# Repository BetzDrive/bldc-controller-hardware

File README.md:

# Betz Drive - A BLDC Controller

This board is designed for low-speed, high torque motor applications that require
highly precise positional and torque commands.

## Features

 * Chainable Initialization. Input/output connectors and 'disco-bus' pins provide
 dynamic initialization, allowing for easy replacement of any board (no hard coded ids).
 
 * High Precision Current Readings
 
 * 12-bit Precision Positional Readings [AS5047U-HTSM](https://ams.com/documents/20143/36005/AS5047U_DS000637_1-00.pdf)
 
 * Thermal Sensitivity
 
 * Optional 20-pin header with 9 GPIO pins, I2C, 3.3V rail, and ground for add-on functionality!
 
## Renderings

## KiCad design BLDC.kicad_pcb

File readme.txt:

File names:
bldc-controller-B.Cu.gbr: Bottom copper
bldc-controller-B.Mask.gbr: Bottom soldermask
bldc-controller-B.Paste.gbr: Bottom paste stencil
bldc-controller-B.SilkS.gbr: Bottom silkscreen
bldc-controller-F.Cu.gbr: Top copper
bldc-controller-F.Mask.gbr: Top soldermask
bldc-controller-F.Paste.gbr: Top paste stencil
bldc-controller-F.SilkS.gbr: Top silkscreen
bldc-controller-In1.Cu.gbr: Inner layer adjacent to top
bldc-controller-In2.Cu.gbr: Inner layer adjacent to bottom
bldc-controller.drl: Drill file

Notes:
EDA software: KiCad
Overall board dimensions: 60 mm x 60 mm (2.36 x 2.36 in)
The two narrow (13 x 0.5 mm) "pads" on the bottom layer are part of a net tie and should be covered by soldermask.

Contact information:
<EMAIL ADDRESS>
<PHONE NUMBER>

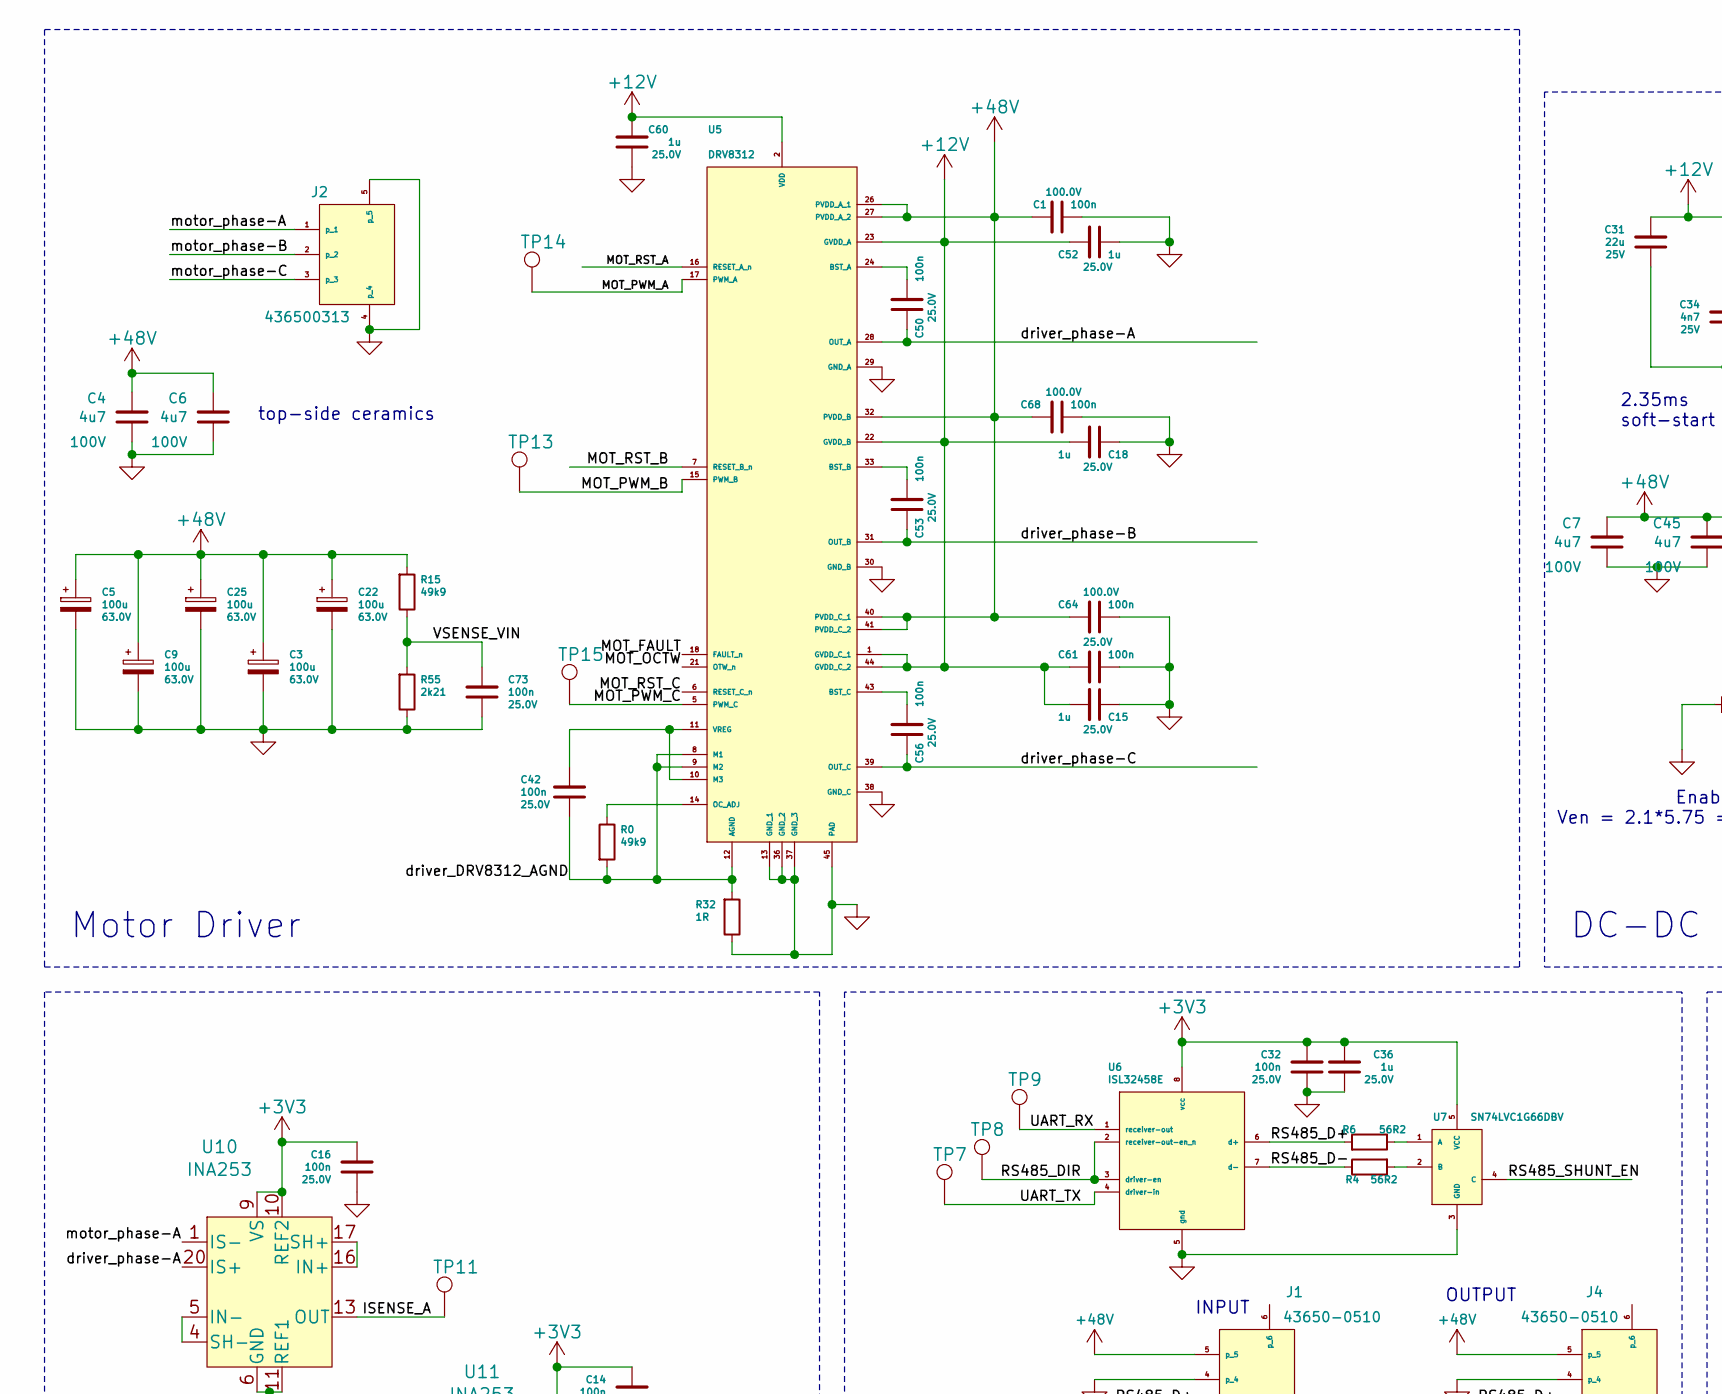
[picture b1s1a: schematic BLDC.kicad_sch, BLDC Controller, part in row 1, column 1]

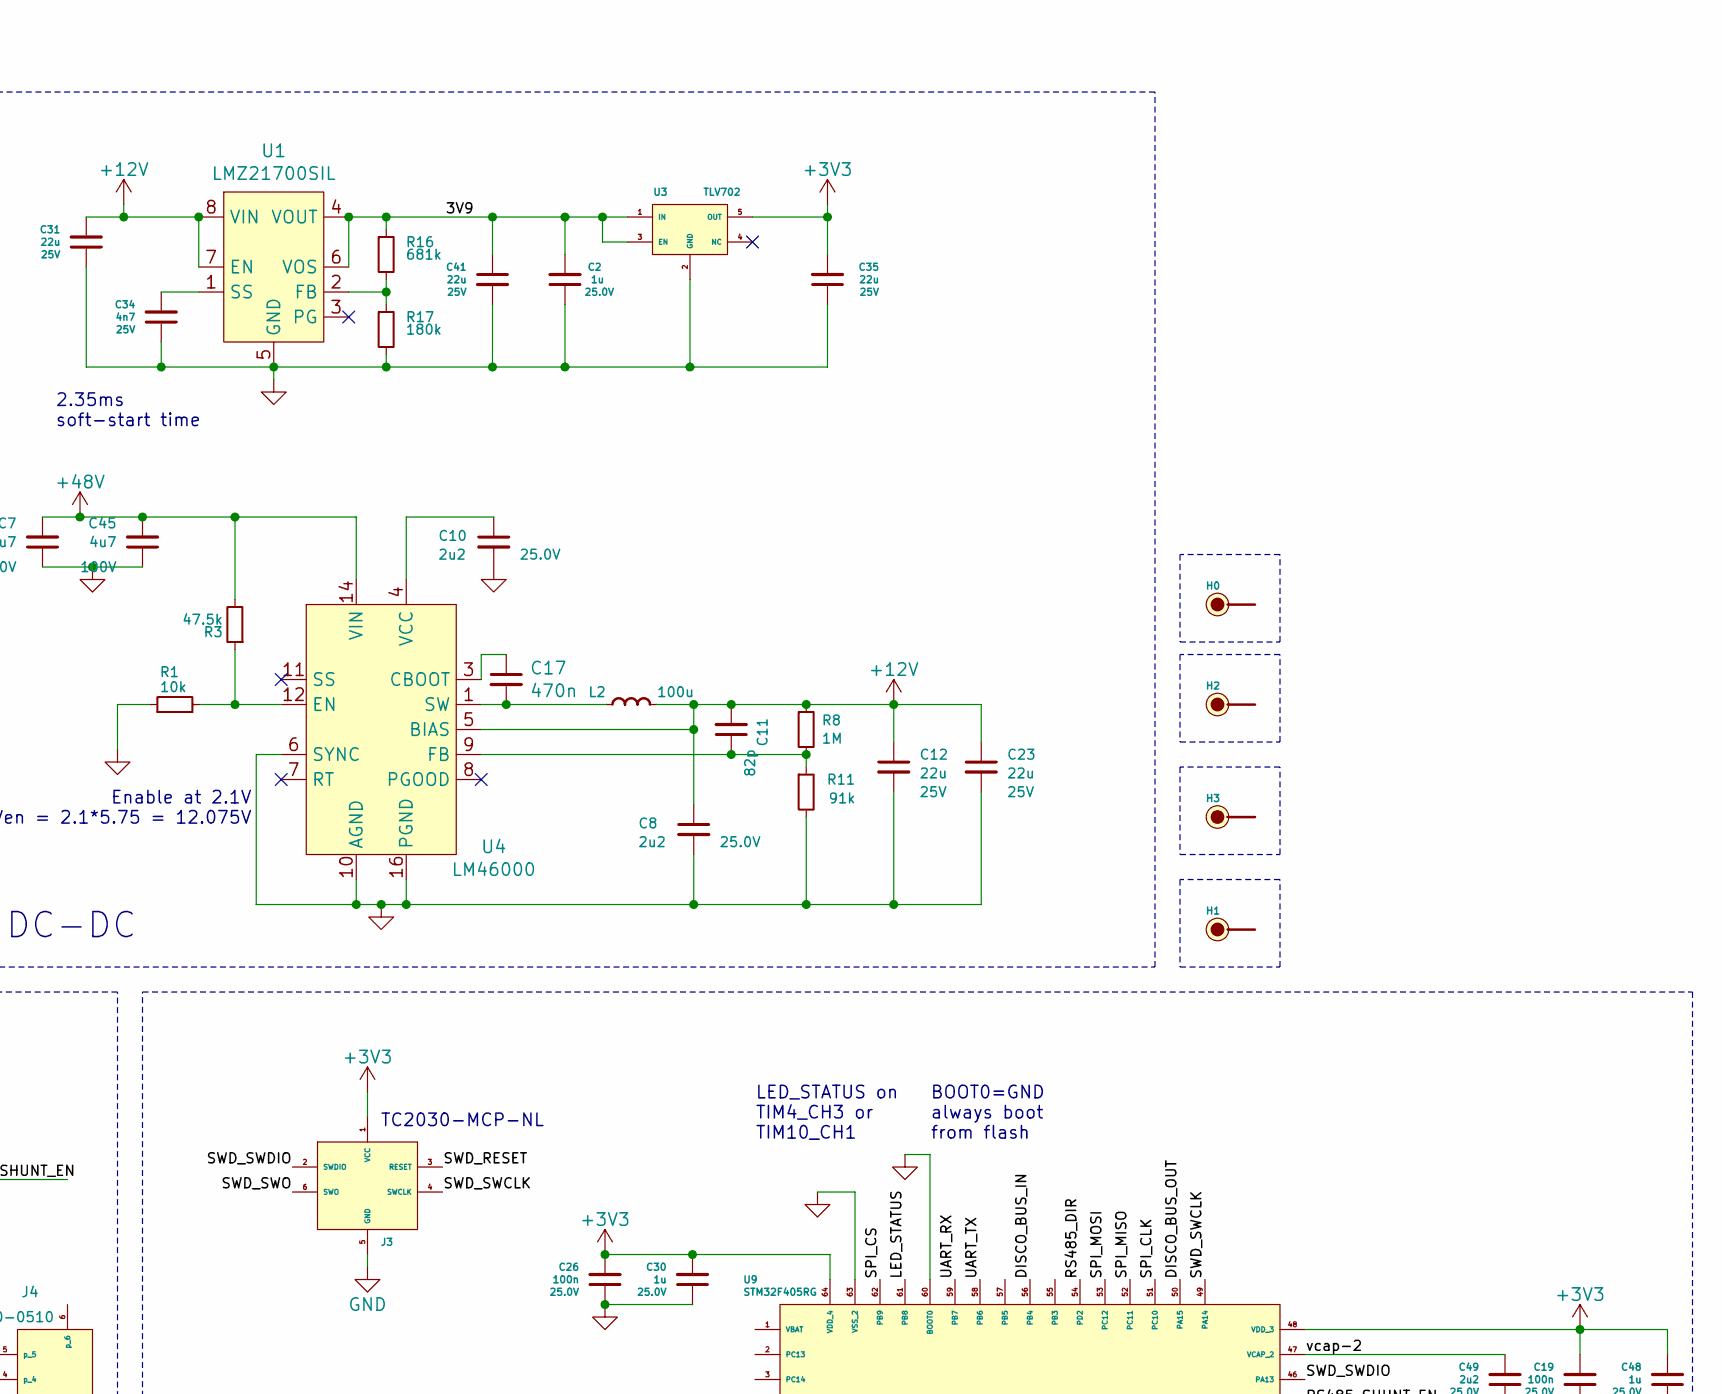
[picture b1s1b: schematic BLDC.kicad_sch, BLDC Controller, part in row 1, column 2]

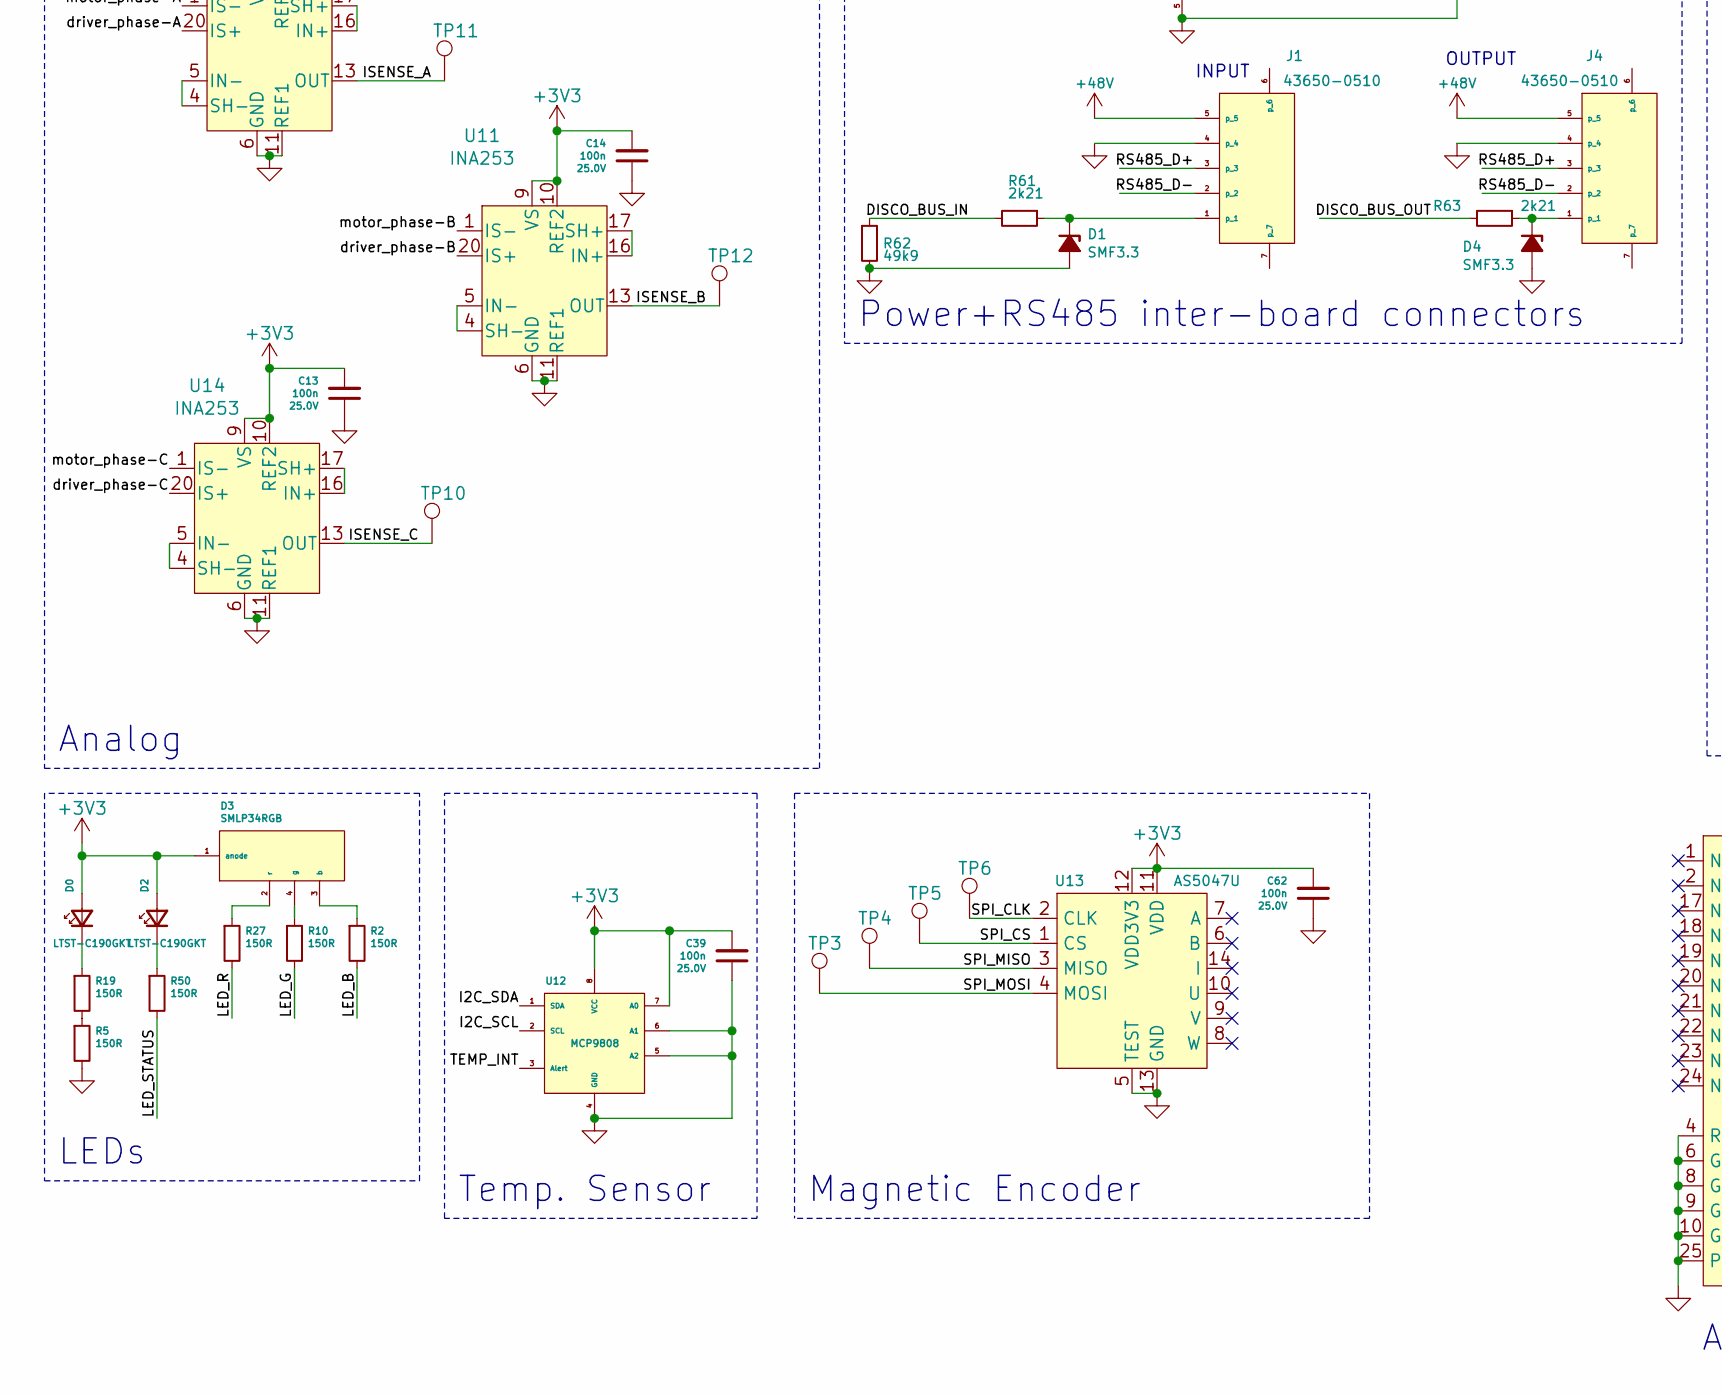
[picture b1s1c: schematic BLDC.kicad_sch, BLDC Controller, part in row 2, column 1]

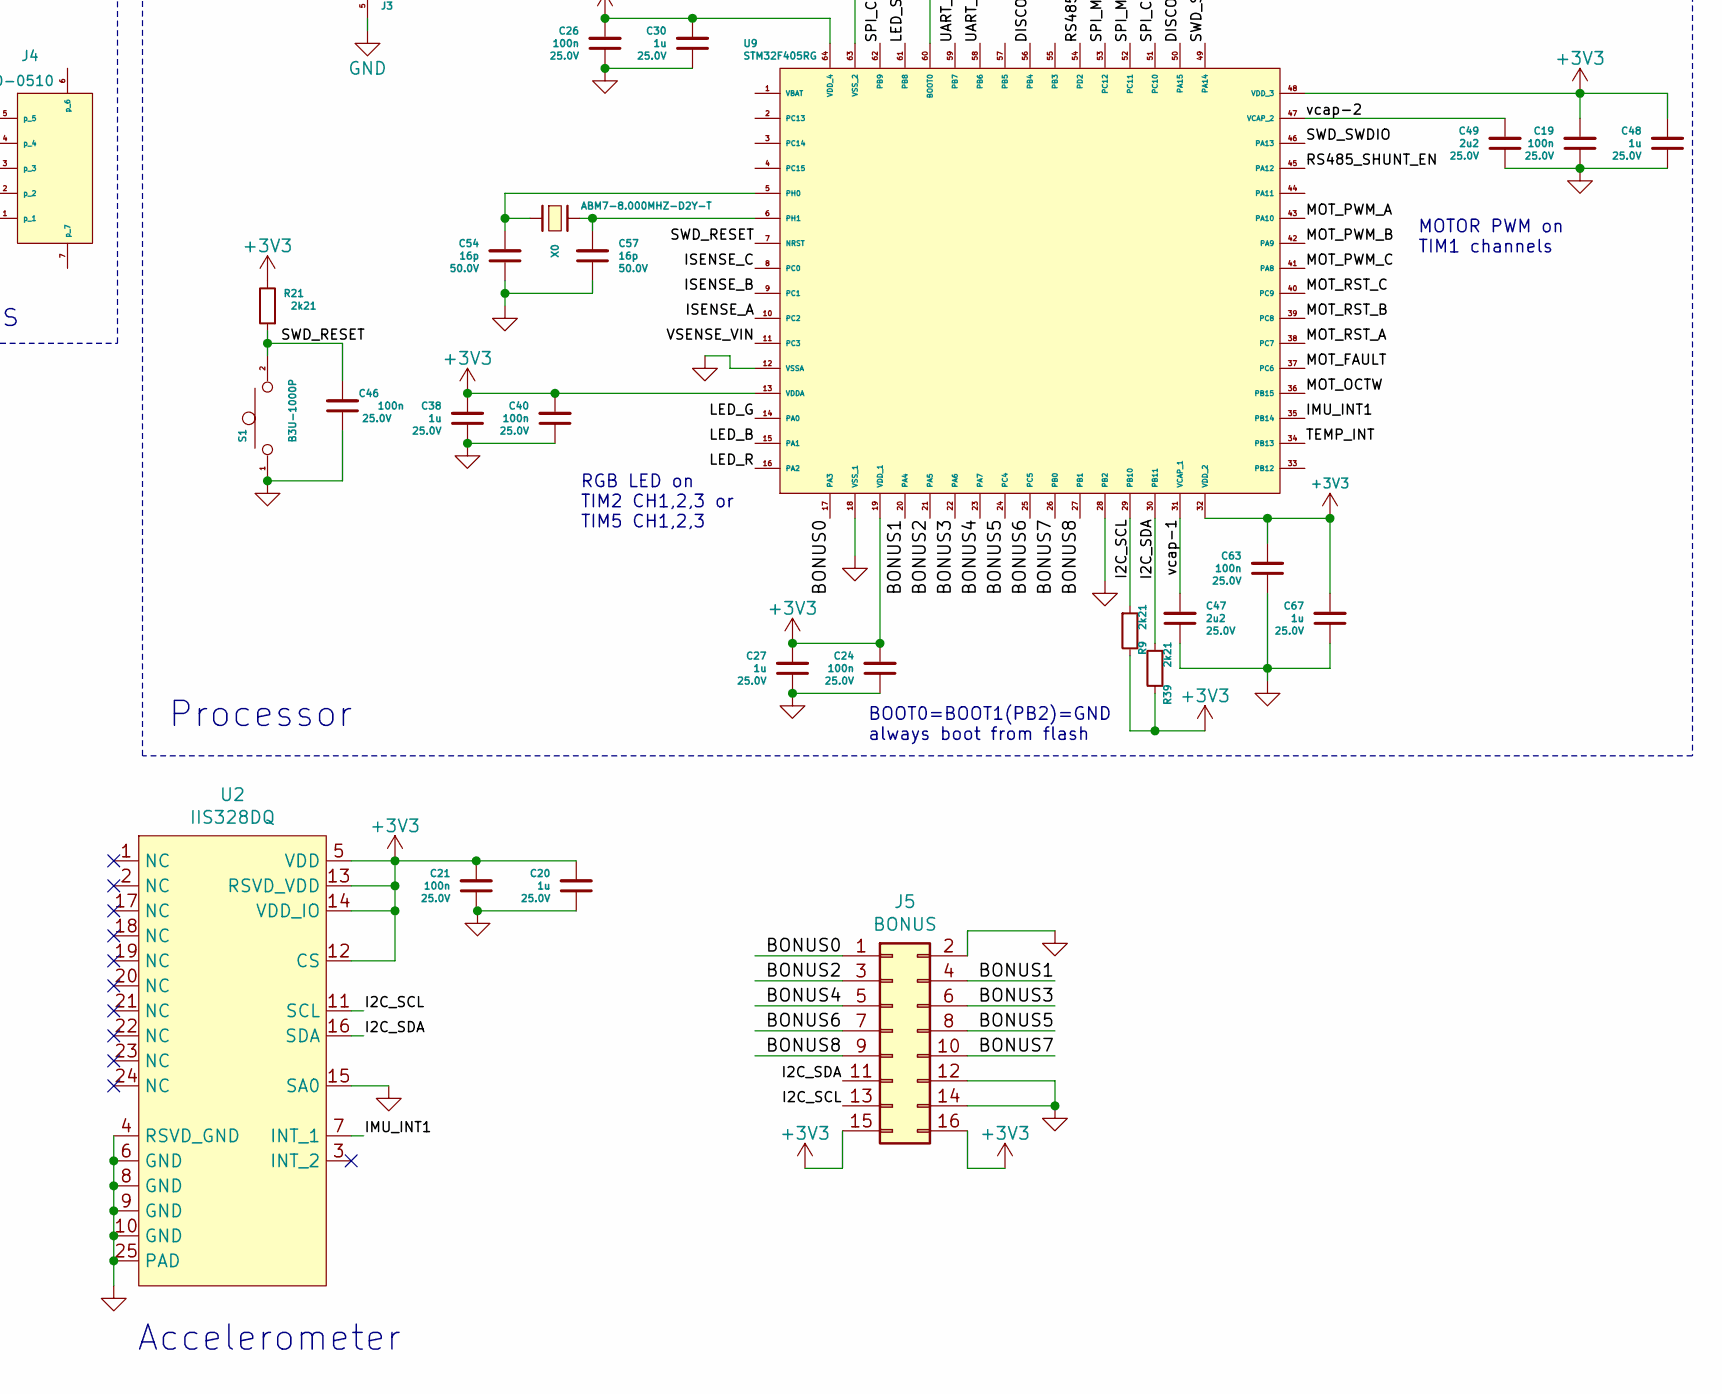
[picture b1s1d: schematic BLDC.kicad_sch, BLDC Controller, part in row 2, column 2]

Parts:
C1, C64, C68: 100n; C_0603_1608Metric; Maximum Voltage 100.0V; Tolerance 10%; MPN CL10B104KC8NNNC
C2, C15, C18, C20, C27, C30, C36, C38, C48, C52, C60, C67: 1u; C_0402_1005Metric; Maximum Voltage 25.0V; Tolerance 10%; MPN GRM155R61E105KA12D
C3, C5, C9, C22, C25: 100u; CP_Elec_10x10; Maximum Voltage 63.0V; Tolerance 20%; MPN EEE-1JA101P
C4, C6, C7, C45: 4u7; C_1210_3225Metric; Maximum Voltage 100V; Tolerance 10%; MPN C3225X7S2A475K200AB
C8, C10, C47, C49: 2u2; C_0402_1005Metric; Maximum Voltage 25.0V; Tolerance 10%; MPN GRM155R61E225KE11D
C11: 82p; C_0402_1005Metric; Maximum Voltage 50V; Tolerance 10%; MPN 04025A820FAT2A
C12, C23, C31, C35, C41: 22u; C_1210_3225Metric; Maximum Voltage 25V; Tolerance 10%; MPN CL32A226KAJNNNE
C13, C14, C16, C19, C21, C24, C26, C32, C39, C40, C42, C46, C50, C53, C56, C61, C62, C63, C73: 100n; C_0402_1005Metric; Maximum Voltage 25.0V; Tolerance 10%; MPN CL05A104KA5NNNC
C17: 470n; C_0402_1005Metric; Maximum Voltage 10.0V; Tolerance 10%; MPN CL05A474KP5NNNC
C34: 4n7; C_0402_1005Metric; Maximum Voltage 25V; Tolerance 10%; MPN CC0402KRX7R8BB472
C54, C57: 16p; C_0402_1005Metric; Maximum Voltage 50.0V; Tolerance 5%; MPN GJM1555C1H160GB01D
D0, D2: LTST-C190GKT; D_0603_1608Metric; MPN LTST-C190GKT
D1, D4: SMF3.3; D_SOD-123F; MPN SMF3.3
D3: SMLP34RGB; rhom-SMLP34RGB-fp; MPN SMLP34RGB2W3
H0, H1, H2, H3: NONE; mounting-hole-pkg
J1, J4: 43650-0510; molex-436500511; MPN 436500510
J2: 436500313; molex-microfit-3-pkg; MPN 436500313
J3: DNP; TC2030-MCP-NL-pkg; MPN DNP
J5: BONUS; PinHeader_2x08_P2.54mm_Horizontal; MPN DNP
L2: 100u; L_7.3x7.3_H4.5; Tolerance 20%; MPN 744777920
R0, R15, R62: 49k9; R_0603_1608Metric; Tolerance 1%; MPN ERJ-3EKF4992V
R1: 10k; R_0402_1005Metric; Tolerance 1%; MPN AC0402FR-0710KL
R2, R5, R10, R19, R27, R50: 150R; R_0402_1005Metric; Tolerance 1%; MPN ERJ-2RKF1500X
R3: 47.5k; R_0402_1005Metric; Tolerance 1%; MPN RC0402FR-0747K5L
R4, R6: 56R2; R_0402_1005Metric; Tolerance 1%; MPN RC0402FR-0756R2L
R8: 1M; R_0402_1005Metric; Tolerance 1%; MPN RC0402FR-071ML
R9, R21, R39, R55, R61, R63: 2k21; R_0402_1005Metric; Tolerance 1%; MPN ERJ-2RKF2211X
R11: 91k; R_0402_1005Metric; Tolerance 1%; MPN RC0402FR-0791KL
R16: 681k; R_0402_1005Metric; Tolerance 1%; MPN RC0402FR-07681KL
R17: 180k; R_0402_1005Metric; Tolerance 1%; MPN RC0402FR-07180KL
R32: 1R; R_0805_2012Metric; Tolerance 1%; MPN ERJ-6DQF1R0V
S1: B3U-1000P; SW_B3U-1000P; MPN B3U-1000P
TP3, TP4, TP5, TP6, TP7, TP8, TP9, TP10, TP11, TP12, TP13, TP14, TP15: TestPoint; TestPoint_Pad_D1.0mm
U1: LMZ21700SIL; SIL0008E; MPN LMZ21700SILR
U2: IIS328DQ; QFN-24-1EP_4x4mm_P0.5mm_EP2.6x2.6mm; MPN IIS328DQTR
U3: TLV702; SOT-23-5; MPN TLV70233DBVR
U4: LM46000; PWP0016G; MPN LM46000PWPR
U5: DRV8312; HTSSOP-44; MPN DRV8312DDWR
U6: ISL32458E; SOIC-8_3.9x4.9mm_P1.27mm; MPN ISL32458EIBZ-T7A
U7: SN74LVC1G66DBV; SOT-23-5; MPN SN74LVC1G66DBV
U9: STM32F405RG; LQFP-64_10x10mm_P0.5mm; MPN STM32F405RGT6
U10, U11, U14: INA253; TSSOP-20_4.4x6.5mm_P0.65mm; MPN INA253A2IPW
U12: MCP9808; MSOP-8_3x3mm_P0.65mm; MPN MCP9808T-E/MS
U13: AS5047U; TSSOP-14_4.4x5mm_P0.65mm; MPN AS5047U-HTSM
X0: ABM7-8.000MHZ-D2Y-T; ABM7-8MHZ-D2Y-T-pkg; MPN ABM7-8.000MHZ-D2Y-T

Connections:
+3V3: C13.2, C14.2, C16.2, C19.2, C20.2, C21.2, C24.2, C26.2, C27.2, C30.2, C32.2, C35.2, C36.2, C38.2, C39.2, C40.2, C48.2, C62.2, C63.2, C67.2, D0.2 (A), D2.2 (A), D3.1 (anode), J3.1 (VCC), J5.15, J5.16, R9.2, R21.2, R39.2, U2.5 (VDD), U2.12 (CS), U2.13 (RSVD_VDD), U2.14 (VDD_IO), U3.5 (OUT), U6.8 (vcc), U7.5 (VCC), U9.13 (VDDA), U9.19 (VDD_1), U9.32 (VDD_2), U9.48 (VDD_3), U9.64 (VDD_4), U10.9 (VS), U10.10 (REF2), U11.9 (VS), U11.10 (REF2), U12.7 (A0), U12.8 (VCC), U13.11 (VDD), U13.12 (VDD3V3), U14.9 (VS), U14.10 (REF2)
+12V: C8.1, C11.2, C12.1, C15.2, C18.2, C23.1, C31.2, C52.2, C60.2, C61.2, L2.2 (p), R8.1, U1.7 (EN), U1.8 (VIN), U4.5 (BIAS), U5.1 (GVDD_C_1), U5.2 (VDD), U5.22 (GVDD_B), U5.23 (GVDD_A), U5.44 (GVDD_C_2)
+48V: C1.2, C3.1, C4.2, C5.1, C6.2, C7.2, C9.1, C22.1, C25.1, C45.2, C64.2, C68.2, J1.5 (p), J4.5 (p), R3.2, R15.1, U4.13 (VIN), U4.14 (VIN), U5.26 (PVDD_A_1), U5.27 (PVDD_A_2), U5.32 (PVDD_B), U5.40 (PVDD_C_1), U5.41 (PVDD_C_2)
/3V9: C2.2, C41.1, R16.1, U1.4 (VOUT), U1.6 (VOS), U3.1 (IN), U3.3 (EN)
/BONUS0: J5.1, U9.17 (PA3)
/BONUS1: J5.4, U9.20 (PA4)
/BONUS2: J5.3, U9.21 (PA5)
/BONUS3: J5.6, U9.22 (PA6)
/BONUS4: J5.5, U9.23 (PA7)
/BONUS5: J5.8, U9.24 (PC4)
/BONUS6: J5.7, U9.25 (PC5)
/BONUS7: J5.10, U9.26 (PB0)
/BONUS8: J5.9, U9.27 (PB1)
/DISCO_BUS_IN: R61.2, R62.1, U9.56 (PB4)
/DISCO_BUS_OUT: R63.2, U9.50 (PA15)
/I2C_SCL: J5.13, R9.1, U2.11 (SCL), U9.29 (PB10), U12.2 (SCL)
/I2C_SDA: J5.11, R39.1, U2.16 (SDA), U9.30 (PB11), U12.1 (SDA)
/IMU_INT1: U2.7 (INT_1), U9.35 (PB14)
/ISENSE_A: TP11.1, U9.10 (PC2), U10.13 (OUT)
/ISENSE_B: TP12.1, U9.9 (PC1), U11.13 (OUT)
/ISENSE_C: TP10.1, U9.8 (PC0), U14.13 (OUT)
/LED_B: R2.2, U9.15 (PA1)
/LED_G: R10.2, U9.14 (PA0)
/LED_R: R27.2, U9.16 (PA2)
/LED_STATUS: R50.2, U9.61 (PB8)
/MOT_FAULT: U5.18 (FAULT_n), U9.37 (PC6)
/MOT_OCTW: U5.21 (OTW_n), U9.36 (PB15)
/MOT_PWM_A: TP14.1, U5.17 (PWM_A), U9.43 (PA10)
/MOT_PWM_B: TP13.1, U5.15 (PWM_B), U9.42 (PA9)
/MOT_PWM_C: TP15.1, U5.5 (PWM_C), U9.41 (PA8)
/MOT_RST_A: U5.16 (RESET_A_n), U9.38 (PC7)
/MOT_RST_B: U5.7 (RESET_B_n), U9.39 (PC8)
/MOT_RST_C: U5.6 (RESET_C_n), U9.40 (PC9)
/RS485_D+: J1.3 (p), J4.3 (p), R6.1, U6.6 (d+)
/RS485_D-: J1.2 (p), J4.2 (p), R4.2, U6.7 (d-)
/RS485_DIR: TP8.1, U6.2 (receiver-out-en_n), U6.3 (driver-en), U9.54 (PD2)
/RS485_SHUNT_EN: U7.4 (C), U9.45 (PA12)
/SPI_CLK: TP6.1, U9.51 (PC10), U13.2 (CLK)
/SPI_CS: TP5.1, U9.62 (PB9), U13.1 (CS)
/SPI_MISO: TP4.1, U9.52 (PC11), U13.3 (MISO)
/SPI_MOSI: TP3.1, U9.53 (PC12), U13.4 (MOSI)
/SWD_RESET: C46.2, J3.3 (RESET), R21.1, S1.2, U9.7 (NRST)
/SWD_SWCLK: J3.4 (SWCLK), U9.49 (PA14)
/SWD_SWDIO: J3.2 (SWDIO), U9.46 (PA13)
/SWD_SWO: J3.6 (SWO)
/TEMP_INT: U9.34 (PB13), U12.3 (Alert)
/UART_RX: TP9.1, U6.1 (receiver-out), U9.59 (PB7)
/UART_TX: TP7.1, U6.4 (driver-in), U9.58 (PB6)
/VSENSE_VIN: C73.2, R15.2, R55.1, U9.11 (PC3)
/driver_DRV8312_AGND: C42.1, R0.1, R32.1, U5.8 (M1), U5.9 (M2), U5.12 (AGND)
/driver_phase-A: C50.1, U5.28 (OUT_A), U10.18 (IS+), U10.19 (IS+), U10.20 (IS+)
/driver_phase-B: C53.1, U5.31 (OUT_B), U11.18 (IS+), U11.19 (IS+), U11.20 (IS+)
/driver_phase-C: C56.1, U5.39 (OUT_C), U14.18 (IS+), U14.19 (IS+), U14.20 (IS+)
/motor_phase-A: J2.1 (p), U10.1 (IS-), U10.2 (IS-), U10.3 (IS-)
/motor_phase-B: J2.2 (p), U11.1 (IS-), U11.2 (IS-), U11.3 (IS-)
/motor_phase-C: J2.3 (p), U14.1 (IS-), U14.2 (IS-), U14.3 (IS-)
/vcap-1: C47.2, U9.31 (VCAP_1)
/vcap-2: C49.2, U9.47 (VCAP_2)
GND: C1.1, C2.1, C3.2, C4.1, C5.2, C6.1, C7.1, C8.2, C9.2, C10.2, C12.2, C13.1, C14.1, C15.1, C16.1, C18.1, C19.1, C20.1, C21.1, C22.2, C23.2, C24.1, C25.2, C26.1, C27.1, C30.1, C31.1, C32.1, C34.1, C35.1, C36.1, C38.1, C39.1, C40.1, C41.2, C45.1, C46.1, C47.1, C48.1, C49.1, C52.1, C54.1, C57.1, C60.1, C61.1, C62.1, C63.1, C64.1, C67.1, C68.1, C73.1, D1.2 (A), D4.2 (A), J1.4 (p), J2.4 (p), J2.5 (p), J3.5 (GND), J4.4 (p), J5.2, J5.12, J5.14, R1.1, R5.2, R11.2, R17.2, R32.2, R55.2, R62.2, S1.1, U1.5 (GND), U1.9 (PAD), U2.4 (RSVD_GND), U2.6 (GND), U2.8 (GND), U2.9 (GND), U2.10 (GND), U2.15 (SA0), U2.25 (PAD), U3.2 (GND), U4.6 (SYNC), U4.10 (AGND), U4.15 (PGND), U4.16 (PGND), U4.17 (AGND), U5.13 (GND_1), U5.29 (GND_A), U5.30 (GND_B), U5.36 (GND_2), U5.37 (GND_3), U5.38 (GND_C), U5.45 (PAD), U6.5 (gnd), U7.3 (GND), U9.12 (VSSA), U9.18 (VSS_1), U9.28 (PB2), U9.60 (BOOT0), U9.63 (VSS_2), U10.6 (GND), U10.11 (REF1), U10.15 (RES), U11.6 (GND), U11.11 (REF1), U11.15 (RES), U12.4 (GND), U12.5 (A2), U12.6 (A1), U13.5 (TEST), U13.13 (GND), U14.6 (GND), U14.11 (REF1), U14.15 (RES)
unnamed: C10.1, U4.4 (VCC)
unnamed: C11.1, R8.2, R11.1, U4.9 (FB)
unnamed: C17.1, U4.3 (CBOOT)
unnamed: C17.2, L2.1 (p), U4.1 (SW), U4.2 (SW)
unnamed: C34.2, U1.1 (SS)
unnamed: C42.2, U5.10 (M3), U5.11 (VREG)
unnamed: C50.2, U5.24 (BST_A)
unnamed: C53.2, U5.33 (BST_B)
unnamed: C54.2, U9.5 (PH0), X0.1 (p)
unnamed: C56.2, U5.43 (BST_C)
unnamed: C57.2, U9.6 (PH1), X0.2 (p)
unnamed: D0.1 (K), R19.1
unnamed: D1.1 (K), J1.1 (p), R61.1
unnamed: D2.1 (K), R50.1
unnamed: D3.2 (r), R27.1
unnamed: D3.3 (b), R2.1
unnamed: D3.4 (g), R10.1
unnamed: D4.1 (K), J4.1 (p), R63.1
unnamed: R0.2, U5.14 (OC_ADJ)
unnamed: R1.2, R3.1, U4.12 (EN)
unnamed: R4.1, U7.2 (B)
unnamed: R6.2, U7.1 (A)
unnamed: R16.2, R17.1, U1.2 (FB)
unnamed: R5.1, R19.2
unnamed: U10.4 (SH-), U10.5 (IN-)
unnamed: U10.16 (IN+), U10.17 (SH+)
unnamed: U11.4 (SH-), U11.5 (IN-)
unnamed: U11.16 (IN+), U11.17 (SH+)
unnamed: U14.4 (SH-), U14.5 (IN-)
unnamed: U14.16 (IN+), U14.17 (SH+)

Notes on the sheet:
Analog
Motor Driver
Magnetic Encoder
TC2030-MCP-NL
Temp. Sensor
MOTOR PWM on TIM1 channels
RGB LED on TIM2 CH1,2,3 or TIM5 CH1,2,3
2.35ms soft-start time
LED_STATUS on TIM4_CH3 or TIM10_CH1
Accelerometer
BOOT0=GND always boot from flash
INPUT
DC-DC
LEDs
BOOT0=BOOT1(PB2)=GND always boot from flash
Enable at 2.1V Ven = 2.1*5.75 = 12.075V
Power+RS485 inter-board connectors
OUTPUT
top-side ceramics
Processor

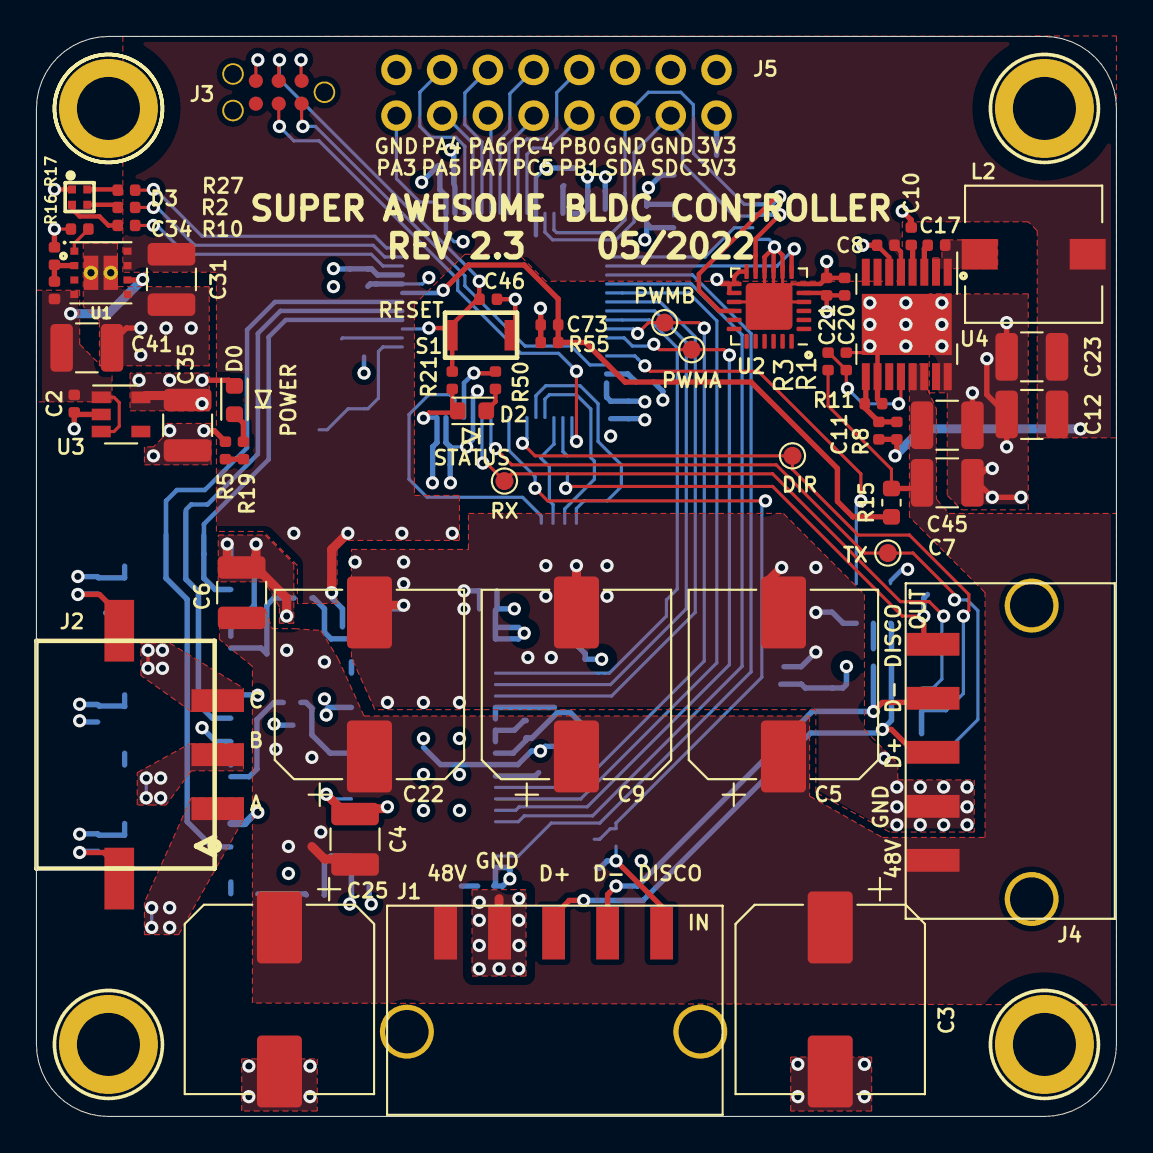
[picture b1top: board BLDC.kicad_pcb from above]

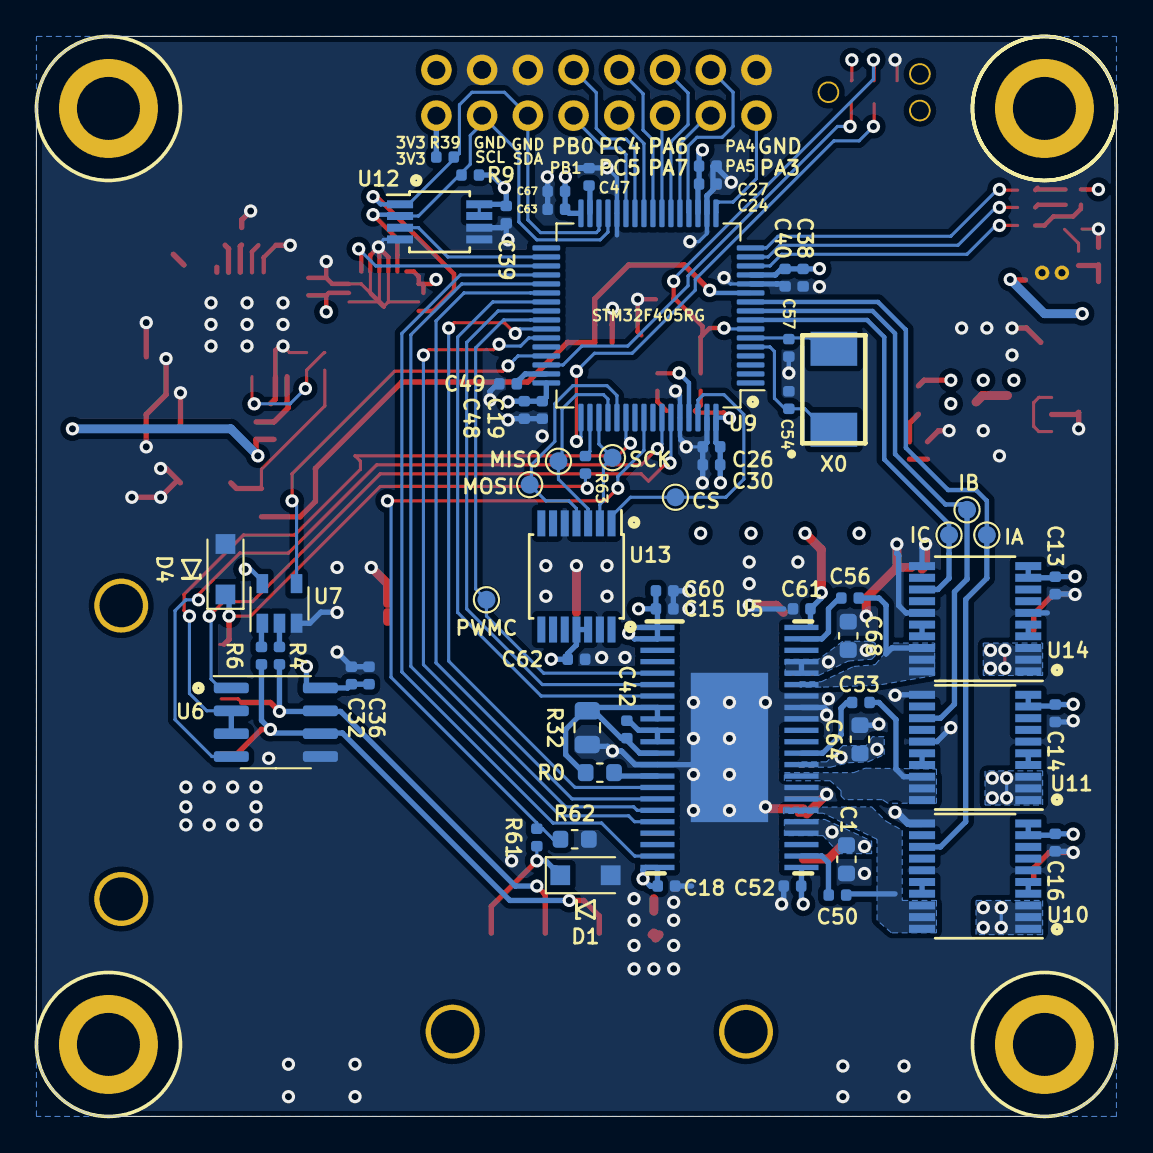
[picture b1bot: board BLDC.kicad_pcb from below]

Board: 4 copper layers, 60.0 x 60.0 mm, 124 parts (62 on the bottom side), 88 nets.

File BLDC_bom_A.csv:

Component,Quantity Per PCB,References,Value,Footprint,Tolerance,MFN,MPN,D1N,D1PN,Maximum Voltage,Maximum Power
1,3,C1 C64 C68,100n,C_0603_1608Metric,10%,Samsung,CL10B104KC8NNNC,Digikey,1276-6807-1-ND,100.0V,
2,19,C13 C14 C16 C19 C21 C24 C26 C32 C39 C40 C42 C46 C50 C53 C56 C61 C62 C63 C73,100n,C_0402_1005Metric,10%,Samsung,CL05A104KA5NNNC,Digikey,1276-1043-1-ND,25.0V,
3,5,C3 C5 C9 C22 C25,100u,CP_Elec_10x10,20%,Panasonic,EEE-1JA101P,Digikey,PCE3942CT-ND,63.0V,
4,2,C54 C57,16p,C_0402_1005Metric,5%,Murata,GJM1555C1H160GB01D,Digikey,490-8081-1-ND,50.0V,
5,12,C2 C15 C18 C20 C27 C30 C36 C38 C48 C52 C60 C67,1u,C_0402_1005Metric,10%,Murata,GRM155R61E105KA12D,Digikey,490-10017-1-ND,25.0V,
6,5,C12 C23 C31 C35 C41,22u,C_1210_3225Metric,10%,Samsung,CL32A226KAJNNNE,Digikey,1276-1101-1-ND,25V,
7,4,C8 C10 C47 C49,2u2,C_0402_1005Metric,10%,Murata,GRM155R61E225KE11D,Digikey,490-12703-1-ND,25.0V,
8,1,C17,470n,C_0402_1005Metric,10%,Samsung,CL05A474KP5NNNC,Digikey,1276-1173-1-ND,10.0V,
9,1,C34,4n7,C_0402_1005Metric,10%,Yageo,CC0402KRX7R8BB472,Digikey,311-1039-1-ND,25V,
10,4,C4 C6 C7 C45,4u7,C_1210_3225Metric,10%,TDK,C3225X7S2A475K200AB,Digikey,445-6042-1-ND,100V,
11,1,C11,82p,C_0402_1005Metric,10%,AVX Corporation,04025A820FAT2A,Digikey,478-10115-1-ND,50V,
12,2,D0 D2,LTST-C190GKT,D_0603_1608Metric,,Lite-On,LTST-C190GKT,Digikey,160-1183-1-ND,,
13,2,D1 D4,SMF3.3,D_SOD-123F,,Littelfuse,SMF3.3,Digikey,F7701CT-ND,,
14,1,D3,SMLP34RGB,rhom-SMLP34RGB-fp,,Rohm,SMLP34RGB2W3,Digikey,SMLP34RGB2W3CT-ND,,
15,2,J1 J4,43650-0510,molex-436500511,,Molex,436500510,Digikey,WM1888CT-ND,,
16,1,J2,436500313,molex-microfit-3-pkg,,Molex,436500313,Digikey,WM1896CT-ND,,
17,1,J5,BONUS,PinHeader_2x08_P2.54mm_Horizontal,,DNP,DNP,DNP,DNP,,
18,1 (DNF),J3,DNP,TC2030-MCP-NL-pkg,,DNP,DNP,DNP,DNP,,
19,1,L2,100u,L_7.3x7.3_H4.5,20%,Wurth,744777920,Digikey,732-1199,,
20,6,R2 R5 R10 R19 R27 R50,150R,R_0402_1005Metric,1%,Panasonic,ERJ-2RKF1500X,Digikey,P150LCT-ND,,0.0625W
21,1,R17,180k,R_0402_1005Metric,1%,Yageo,RC0402FR-07180KL,Digikey,311-180KLRCT-ND,,0.0625W
22,1,R8,1M,R_0402_1005Metric,1%,Yageo,RC0402FR-071ML,Digikey,311-1.00MLRCT-ND,,0.0625W
23,1,R32,1R,R_0805_2012Metric,1%,Panasonic,ERJ-6DQF1R0V,Digikey,P19268CT-ND,,0.333W
24,6,R9 R21 R39 R55 R61 R63,2k21,R_0402_1005Metric,1%,Panasonic,ERJ-2RKF2211X,Digikey,P2.21KLCT-ND,,0.0625W
25,3,R0 R15 R62,49k9,R_0603_1608Metric,1%,Panasonic,ERJ-3EKF4992V,Digikey,P49.9KHCT-ND,,0.0625W
26,2,R4 R6,56R2,R_0402_1005Metric,1%,Yageo,RC0402FR-0756R2L,Digikey,311-56.2LRCT-ND,,0.0625W
27,1,R16,681k,R_0402_1005Metric,1%,Yageo,RC0402FR-07681KL,Digikey,YAG3212CT-ND,,0.0625W
28,1,R11,91k,R_0402_1005Metric,1%,Yageo,RC0402FR-0791KL,Digikey,311-91.0KLRCT-ND,,0.0625W
29,1,S1,B3U-1000P,SW_B3U-1000P,,Omron,B3U-1000P,Digikey,SW1020CT-ND,,
30,1,U13,AS5047U,TSSOP-14_4.4x5mm_P0.65mm,,AMS,AS5047U-HTSM,Mouser,985-AS5047U-HTSM,,
31,1,U5,DRV8312,HTSSOP-44,,TI,DRV8312DDWR,Digikey,296-29649-1-ND,,
32,1,U2,IIS328DQ,QFN-24-1EP_4x4mm_P0.5mm_EP2.6x2.6mm,,ST,IIS328DQTR,Digikey,497-15701-1-ND,,
33,3,U10 U11 U14,INA253,TSSOP-20_4.4x6.5mm_P0.65mm,,TI,INA253A2IPW,Digikey,296-53071-ND,,
34,1,U6,ISL32458E,SOIC-8_3.9x4.9mm_P1.27mm,,Renesas,ISL32458EIBZ-T7A,Digikey,ISL32458EIBZ-T7ACT-ND,,
35,1,U4,LM46000,PWP0016G,,TI,LM46000PWPR,Digikey,296-40222-1-ND,,
36,1,U1,LMZ21700SIL,SIL0008E,,TI,LMZ21700SILR,Digikey,296-44325-1-ND,,
37,1,U12,MCP9808,MSOP-8_3x3mm_P0.65mm,,Microchip,MCP9808T-E/MS,Digikey,MCP9808T-E/MSCT-ND,,
38,1,U7,SN74LVC1G66DBV,SOT-23-5,,TI,SN74LVC1G66DBV,Digikey,296-13253-1-ND,,
39,1,U9,STM32F405RG,LQFP-64_10x10mm_P0.5mm,,ST,STM32F405RGT6,Digikey,497-11767-ND,,
40,1,U3,TLV702,SOT-23-5,,TI,TLV70233DBVR,Digikey,296-32415-1-ND,,
41,1,X0,ABM7-8.000MHZ-D2Y-T,ABM7-8MHZ-D2Y-T-pkg,,Abracon LLC,ABM7-8.000MHZ-D2Y-T,Digikey,535-9831-1-ND,,





Component Groups:,41
Component Count:,105
Fitted Components:,104
Number of PCBs:,1
Total components:,104
Schematic Version:,A
Schematic Date:,2019-08-22
PCB Variant:,['default']
BoM Date:,Mon Oct 14 13:54:15 2019
Schematic Source:,/home/mquigley/hw/bldc-controller-hardware/BLDC.sch
KiCad Version:,Eeschema 5.99.0-unknown-e291576~100~ubuntu18.04.1

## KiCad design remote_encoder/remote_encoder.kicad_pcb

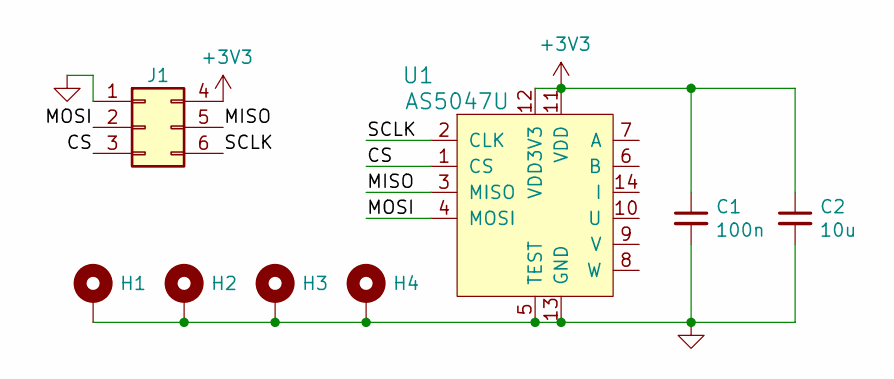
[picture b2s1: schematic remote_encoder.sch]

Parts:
C1: 100n; C_0603_1608Metric
C2: 10u; C_0603_1608Metric
H1, H2, H3, H4: MountingHole_Pad; MountingHole_2.2mm_M2_DIN965_Pad
J1: Conn_02x03_Odd_Even; Molex_Nano-Fit_105314-xx06_2x03_P2.50mm_Horizontal
U1: AS5047U; TSSOP-14_4.4x5mm_P0.65mm

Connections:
+3V3: C1.1, C2.1, J1.4, U1.11 (VDD), U1.12 (VDD3V3)
/CS: J1.3, U1.1 (CS)
/MISO: J1.5, U1.3 (MISO)
/MOSI: J1.2, U1.4 (MOSI)
/SCLK: J1.6, U1.2 (CLK)
GND: C1.2, C2.2, H1.1, H2.1, H3.1, H4.1, J1.1, U1.5 (TEST), U1.13 (GND)

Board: 2 copper layers, 8 parts (1 on the bottom side), 6 nets, no tracks yet.

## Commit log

2019-04-12 Create LICENSE
2019-07-05 Blue V2 hardware merge
2019-07-29 First draft of rework, major changes to placement, routing and components choice
2019-07-31 Breaking changes, changed IO pin assigment of STM32 to simplify routing, various optimizations
2019-08-05 Cleared DRC errors, changed minimum track width to 6 mil for cheaper manufacturing.
2019-08-06 Removed capacitor that would be in contact in 3d mounting, fixed silkscreen
2019-08-08 WIP changed capacitors back to SMT
2019-08-08 Fixed DRC errors, added ground pour, fixed courtyards of connectors and DRV chip to allow more packed designs
2019-08-08 Added ground pour in bottom layer for thermal dissipation and current return
2019-08-08 add a bit more clearance to 48v pour
2019-08-09 Added 3d models for molex connectors
2019-08-09 Changed J1 connector to through hole and moved to middle of PCB
2019-08-09 WIP, adding 3d models, choosing kicad official footprints. TODO fix possible conflict between capacitor and accelerometer / temperature sensor
2019-08-09 Expanded 48V pour, arranged components to reduce risk of collision with capacitors
2019-08-09 Fixed inductor footprints and added 3d models
2019-08-09 Added 3d models for remaining parts
2019-08-09 toying with some major layout changes to move the MCU far away from EMI
2019-08-09 Moving capacitors slightly
2019-08-10 Preliminary routing of new STM position, still to check and refine
2019-08-10 WIP adding output snubbers and trying to improve high-power paths
2019-08-11 finish draft of high-power net routes. clean up throughout.
2019-08-12 minimize rs485 stubs. more power net cleanup. bigger vias.
2019-08-13 massively increase size of ground bus on middle of top layer. use big vias.
2019-08-14 route cleanup and enlarge vias
2019-08-14 WIP simplify power supply designs
2019-08-16 Finished simplified power rail design
2019-08-19 switch to larger accel package. enlarge all vias and traces. clean up.
2019-08-19 Adding In/Out labels to Molex Connectors
2019-08-20 use NRST for SWD_RESET
2019-08-20 add 1v2 reference to INA250 and MCU ADC
2019-08-21 Added BOM
2019-08-22 Added part number and updated capacitance for bulk caps
2019-08-22 add title and current rev of bom generator script
2019-08-22 nicer warnings for safetly-ignored schematic entries
2019-08-22 Added consolidated BoM generated and KiBoM submodule used to generate it
2019-08-23 consolidate lots of BOM line items, lots of clean up
2019-08-23 fix part numbers, move programming connector, add i2c test points
2019-08-23 add test points to SPI bus
2019-08-23 more test points
2019-08-23 PWM test points
2019-08-23 add TVS diodes to input and output disco bus connector pins
2019-08-24 clear out north edge of PCB for upcoming bonus header
2019-08-24 WIP adding bonus header to north edge
2019-08-25 finish up bonus connector
2019-08-25 a bit more pcb cleanup, add slow-start cap MPN and gerbv project
2019-08-25 add fab README and gerbv project
2019-08-25 update BOM file
2019-08-26 Aesthetic, add LMZ regulator 3d model
2019-08-26 a bit of trivial cleanup. sent out for quote
2019-10-04 WIP new revision, change INA250 to INA253 (higher bandwidth), regulator to low EMI version
2019-10-05 tinker with layout, mostly with 12v dc-dc
2019-10-07 Added 3d model for regulator, routed all design (passing DRC)
2019-10-08 place/route tweaks. move accelerometer to top layer.
2019-10-09 Routed I2C, updated BOM
2019-10-09 Cosmetic improvements to silkscreen
2019-10-09 Updated 3d models to include latest inductor
2019-10-14 add another via for each motor-phase trace, and more silkscreen markings
2019-10-14 switch 4u7 to in-stock TDK part number
2019-10-14 export fabrication files for v2.2
2019-12-10 Added 3d models and library for molex connectors
2019-12-10 Added nanofit connector 3d model
2019-12-31 Fixed I2C address of temperature sensor
    TODO regenerate gerber files
2020-03-20 add fixme file
2020-04-18 Initial README. Incomplete.
2020-04-18 3D images
2020-04-18 Adding renderings to readme
2020-04-24 first attempt at placement of minimalist remote encoder PCB
2020-04-27 Initial README (#7)
    * Initial README. Incomplete.
    * 3D images
    * Adding renderings to readme
    * Update README.md
    * Update README.md
2020-07-21 Adjusted LM46000 to start up at gt 12V instead of Vmin
2020-07-22 Correcting voltage divider
2020-09-13 Adjusted LM46000 to start-up at gt 12V instead of Vmin (#8)
    * Adjusted LM46000 to start up at gt 12V instead of Vmin
    * Correcting voltage divider
2020-12-05 Fab files
2020-12-05 Updating label
2020-12-05 Updating to new format files
2020-12-05 Position files and correct extensions for gerbers
2022-05-15 Upgrade to kicad6
2022-05-15 Fix DRC checks
2022-09-23 Kicad6 (#13)
    * Upgrade to kicad6
    * Fix DRC checks
